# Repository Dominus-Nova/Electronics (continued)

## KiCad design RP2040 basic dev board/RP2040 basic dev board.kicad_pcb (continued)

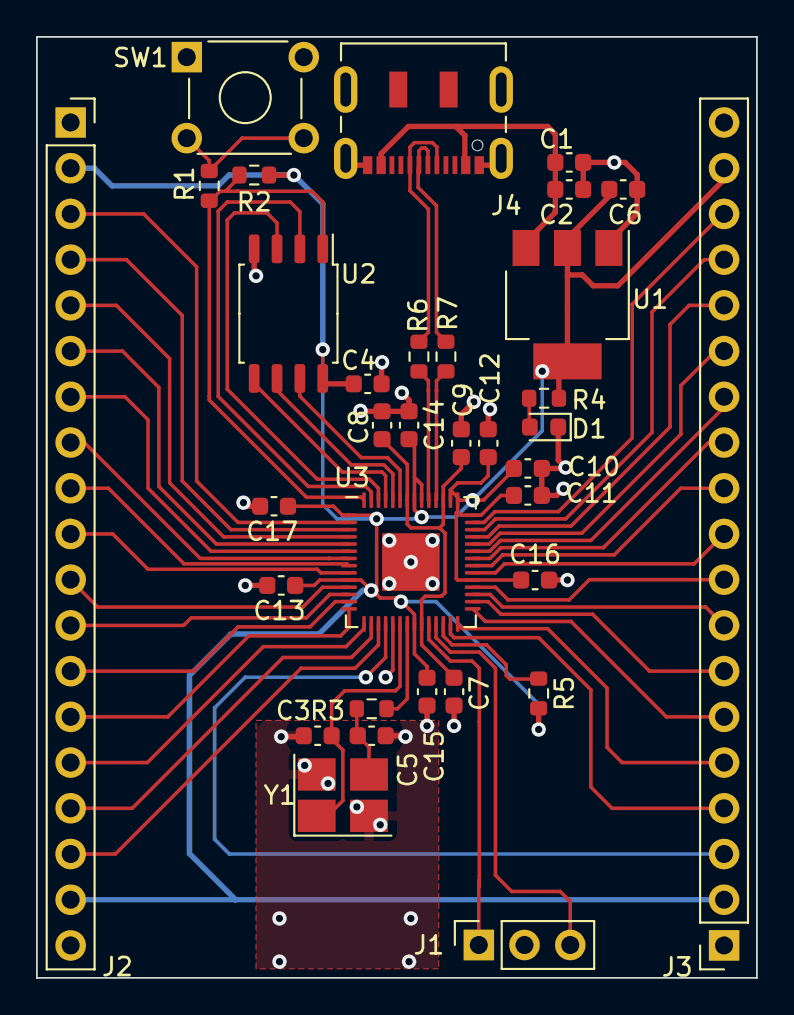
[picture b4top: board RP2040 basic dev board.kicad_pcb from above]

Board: 2 copper layers, 40.0 x 52.3 mm, 34 parts (0 on the bottom side), 52 nets.

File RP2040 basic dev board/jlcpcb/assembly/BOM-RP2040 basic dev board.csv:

Comment,Designator,Footprint,LCSC
5k1,"R6,R7",R_0603_1608Metric,C105580
51p,"C3,C5",C_0603_1608Metric,C107051
22u,C6,C_0603_1608Metric,C109448
10u,C1,C_0603_1608Metric,C109457
100n,"C10,C11,C13,C14,C15,C16,C17,C4,C7,C8",C_0603_1608Metric,C14663
1u,"C12,C2,C9",C_0603_1608Metric,C14664
LED_Green,D1,LED_0603_1608Metric,C188729
RP2040,U3,QFN-56-1EP_7x7mm_P0.4mm_EP3.2x3.2mm,C2040
1k,"R1,R3,R4",R_0603_1608Metric,C22548
AMS1117-3.3,U1,SOT-223-3_TabPin2,C5199435
X322512MSB4SI,Y1,Crystal_SMD_3225-4Pin_3.2x2.5mm_HandSoldering,C9002
SW_Push,SW1,SW_TH_Tactile_Omron_B3F-10xx,C93157
W25Q128JVS,U2,SOIC-8_5.23x5.23mm_P1.27mm,C97521
serial wire debug,J1,PinSocket_1x03_P2.54mm_Vertical,
gpio 1,J3,PinSocket_1x19_P2.54mm_Vertical,
DNF,R5,R_0603_1608Metric,
gpio 2,J2,PinSocket_1x19_P2.54mm_Vertical,
USB_C_Receptacle_USB2.0,J4,USB_C_Receptacle_JAE_DX07S016JA1R1500,
DNF,R2,R_0603_1608Metric,

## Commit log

2023-02-06 Create README.md
    e
2023-02-08 updated the git pull and push commands to not close after they run
2023-02-08 created new proj: rp2040 basic dev board
2023-03-07 me on my way to make a 4 layer pcb :>>>>>>
2023-03-09 added most major components to schematic, unwired also added any components not in kicad library to the "components library" folder , all have .step files
2023-03-13 dont remember changes, were last night
2023-03-14 some small updates
2023-03-14 added a symbol for the (symbol "E28-2G4M27S" (in_bom yes) (on_board yes) (property "Reference" "U" (id 0) (at 0 0 0) (effects (font (size 1.27 1.27))) ) (property "Value" "E28-2G4M27S" (id 1) (at 6.3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
2023-03-17 did a little trolling, started on the power supply
2023-03-20 finished power and rp2040 pinout
2023-03-21 made a lot of changes, nearly done
2023-03-22 basicly finished schem, need to finalise the rf ant for the gps
2023-03-22 finaly merged the change i wanted, the lora module now has a footprint
2023-03-22 finished schematic
2023-03-23 fixed some 3d shapes
2023-03-23 started component placement, finished placeing power?
2023-03-24 some more component placement
2023-03-25 finished first layout itteration
2023-03-25 started routing
2023-03-26 pcb revision one completed, the png's are for the reddit gods to review.
2023-03-27 got some work to do
2023-03-28 even ore stuff been done, board has been space optimised
2023-03-28 added boost regulator
2023-03-28 started layout for the power part of board, addded some beads to NEO RX/TX
2023-03-29 aaaaa
2023-03-29 revision 2 complete, need to upload for review
2023-03-30 revision 2 complete, need to upload for review sent off rev 2 for review
2023-04-27 bom work
2023-04-27 more stuff done
2023-04-28 pcb done?
2023-07-27 rightio, take two on the pcb.
2023-08-03 stuff
2023-08-09 more pcb fixing
2023-08-09 started pcb layout mk2
2023-09-05 arranged sub units for routing pls dont eat my pcb github
2023-09-07 routed some stuff, E
2023-09-09 added a new test pcb for milling
2023-09-14 remaking calens project for spice sim
2023-09-15 calen pedel
2023-09-22 added some decoupling caps
